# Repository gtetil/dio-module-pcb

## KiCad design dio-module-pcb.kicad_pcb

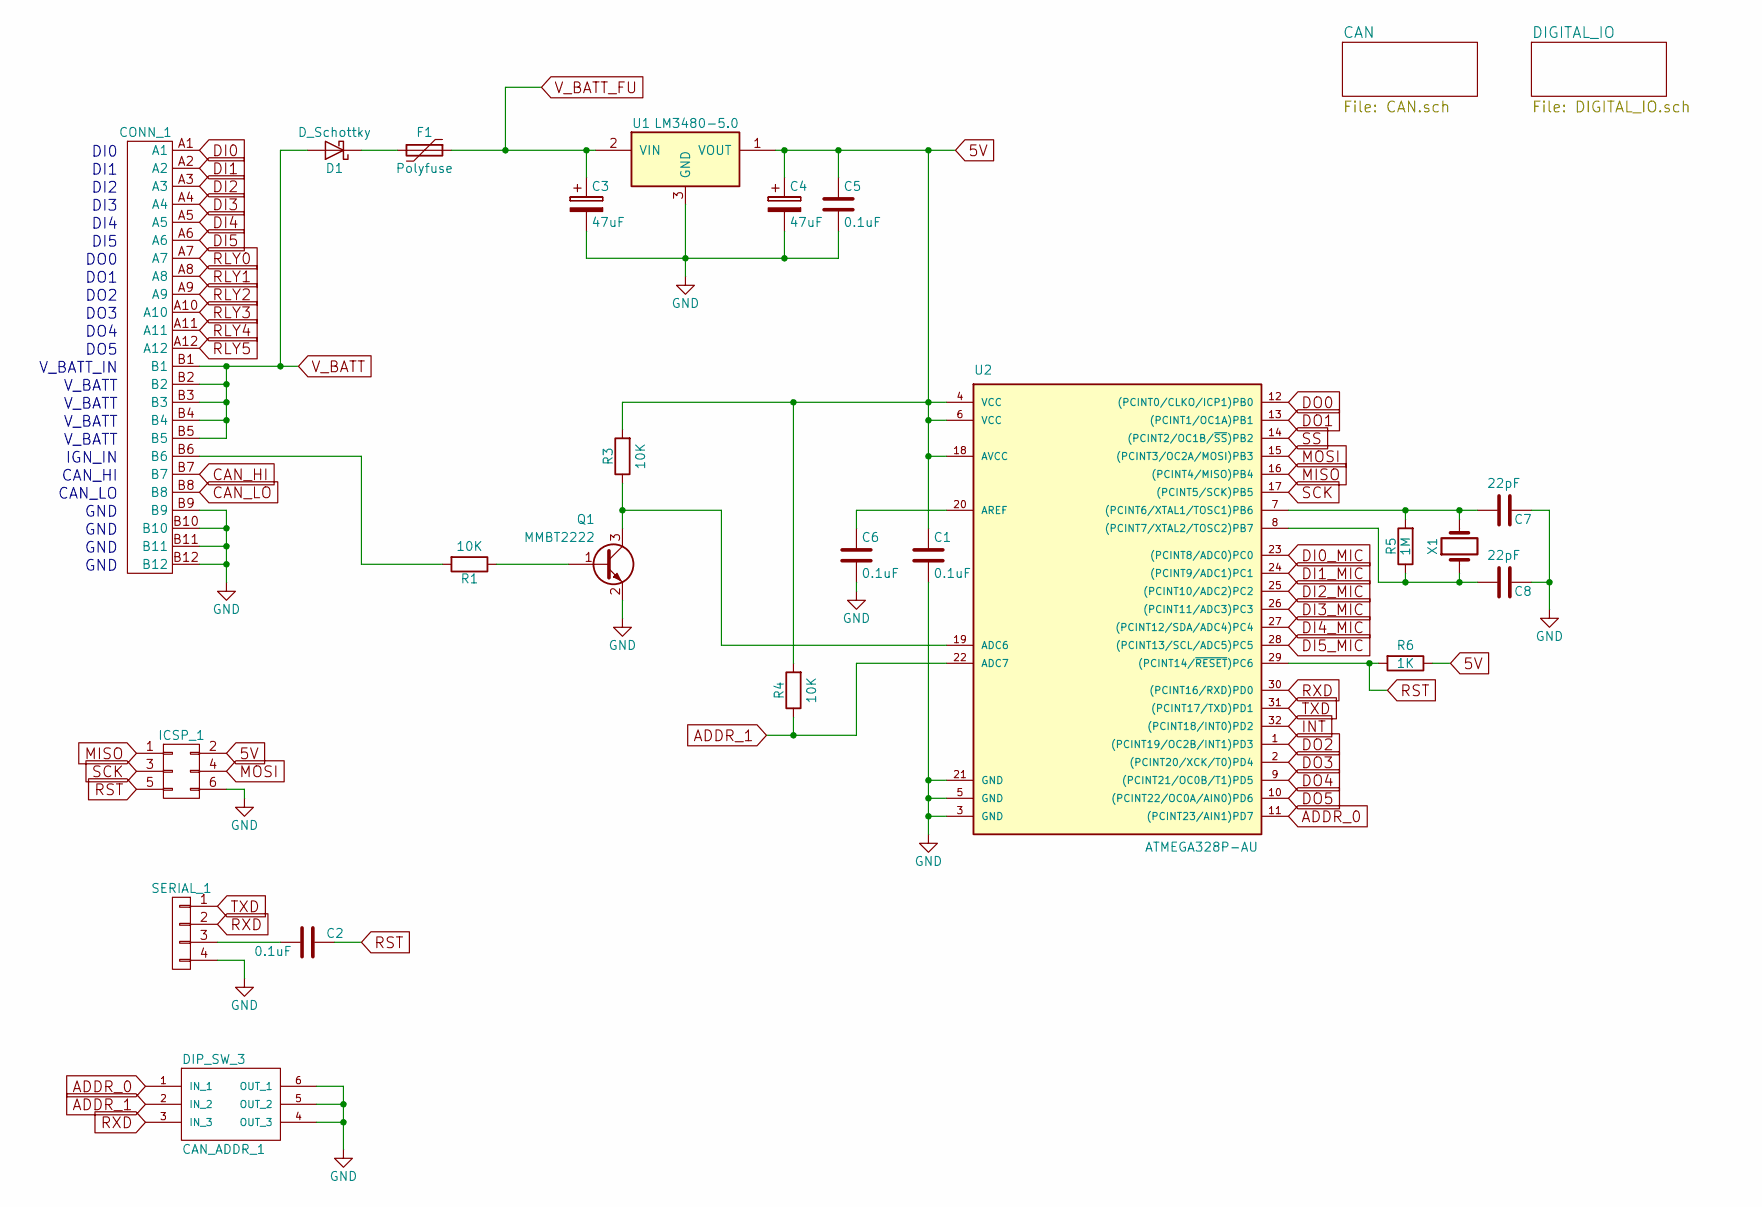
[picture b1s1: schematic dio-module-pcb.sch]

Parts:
C1, C2, C5, C6: 0.1uF; C_0805
C3, C4: 47uF; CP_Elec_6.3x5.3
C7, C8: 22pF; C_0805
CAN_ADDR_1: DIP_SW_3; SW_DIP_x3_W8.61mm_Slide_LowProfile
CONN_1: DEUTSCH_CONN_(DTM13-12PA-12PB-R008)
D1: D_Schottky; DO-214AB
F1: Polyfuse; R_1812
ICSP_1: CONN_02X03; Pin_Header_Straight_2x03_Pitch2.54mm_SMD
Q1: MMBT2222; SOT-23
R1, R3, R4: 10K; R_0805
R5: 1M; R_0805
R6: 1K; R_0805
SERIAL_1: CONN_01X04; Pin_Header_Straight_1x04_Pitch2.54mm_SMD_Pin1Right
U1: LM3480-5.0; SOT-23
U2: ATMEGA328P-AU; TQFP-32_7x7mm_Pitch0.8mm
X1: Crystal; Crystal_SMD_HC49-SD

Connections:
5V: C1.1, C4.1, C5.1, ICSP_1.2, R3.2, R4.2, R6.1, U1.1 (VOUT), U2.4 (VCC), U2.6 (VCC), U2.18 (AVCC); also elsewhere on the board
ADDR_0: CAN_ADDR_1.1 (IN_1), U2.11 ((PCINT23/AIN1)PD7)
ADDR_1: CAN_ADDR_1.2 (IN_2), R4.1, U2.22 (ADC7)
CAN_HI: CONN_1.B7; also elsewhere on the board
CAN_LO: CONN_1.B8; also elsewhere on the board
DI0: CONN_1.A1; also elsewhere on the board
DI0_MIC: U2.23 ((PCINT8/ADC0)PC0); also elsewhere on the board
DI1: CONN_1.A2; also elsewhere on the board
DI1_MIC: U2.24 ((PCINT9/ADC1)PC1); also elsewhere on the board
DI2: CONN_1.A3; also elsewhere on the board
DI2_MIC: U2.25 ((PCINT10/ADC2)PC2); also elsewhere on the board
DI3: CONN_1.A4; also elsewhere on the board
DI3_MIC: U2.26 ((PCINT11/ADC3)PC3); also elsewhere on the board
DI4: CONN_1.A5; also elsewhere on the board
DI4_MIC: U2.27 ((PCINT12/SDA/ADC4)PC4); also elsewhere on the board
DI5: CONN_1.A6; also elsewhere on the board
DI5_MIC: U2.28 ((PCINT13/SCL/ADC5)PC5); also elsewhere on the board
DO0: U2.12 ((PCINT0/CLKO/ICP1)PB0); also elsewhere on the board
DO1: U2.13 ((PCINT1/OC1A)PB1); also elsewhere on the board
DO2: U2.1 ((PCINT19/OC2B/INT1)PD3); also elsewhere on the board
DO3: U2.2 ((PCINT20/XCK/T0)PD4); also elsewhere on the board
DO4: U2.9 ((PCINT21/OC0B/T1)PD5); also elsewhere on the board
DO5: U2.10 ((PCINT22/OC0A/AIN0)PD6); also elsewhere on the board
GND: C1.2, C3.2, C4.2, C5.2, C6.2, C7.1, C8.1, CAN_ADDR_1.4 (OUT_3), CAN_ADDR_1.5 (OUT_2), CAN_ADDR_1.6 (OUT_1), CONN_1.B9, CONN_1.B10, CONN_1.B11, CONN_1.B12, ICSP_1.6, Q1.2 (E), SERIAL_1.4, U1.3 (GND), U2.3 (GND), U2.5 (GND), U2.21 (GND); also elsewhere on the board
INT: U2.32 ((PCINT18/INT0)PD2); also elsewhere on the board
MISO: ICSP_1.1, U2.16 ((PCINT4/MISO)PB4); also elsewhere on the board
MOSI: ICSP_1.4, U2.15 ((PCINT3/OC2A/MOSI)PB3); also elsewhere on the board
unnamed: C2.2, SERIAL_1.3
unnamed: C6.1, U2.20 (AREF)
unnamed: C7.2, R5.2, U2.7 ((PCINT6/XTAL1/TOSC1)PB6), X1.2
unnamed: C8.2, R5.1, U2.8 ((PCINT7/XTAL2/TOSC2)PB7), X1.1
unnamed: CONN_1.B6, R1.2
unnamed: D1.1 (K), F1.2
unnamed: Q1.1 (B), R1.1
unnamed: Q1.3 (C), R3.1, U2.19 (ADC6)
RLY0: CONN_1.A7; also elsewhere on the board
RLY1: CONN_1.A8; also elsewhere on the board
RLY2: CONN_1.A9; also elsewhere on the board
RLY3: CONN_1.A10; also elsewhere on the board
RLY4: CONN_1.A11; also elsewhere on the board
RLY5: CONN_1.A12; also elsewhere on the board
RST: C2.1, ICSP_1.5, R6.2, U2.29 ((PCINT14/~RESET~)PC6)
RXD: CAN_ADDR_1.3 (IN_3), SERIAL_1.2, U2.30 ((PCINT16/RXD)PD0)
SCK: ICSP_1.3, U2.17 ((PCINT5/SCK)PB5); also elsewhere on the board
SS: U2.14 ((PCINT2/OC1B/~SS~)PB2); also elsewhere on the board
TXD: SERIAL_1.1, U2.31 ((PCINT17/TXD)PD1)
V_BATT: CONN_1.B1, CONN_1.B2, CONN_1.B3, CONN_1.B4, CONN_1.B5, D1.2 (A); also elsewhere on the board
V_BATT_FU: C3.1, F1.1, U1.2 (VIN); also elsewhere on the board

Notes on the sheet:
DI0
DI1
DI2
DI3
DI4
DI5
DO0
DO1
DO2
DO3
DO4
DO5
V_BATT_IN
V_BATT
IGN_IN
CAN_HI
CAN_LO
GND

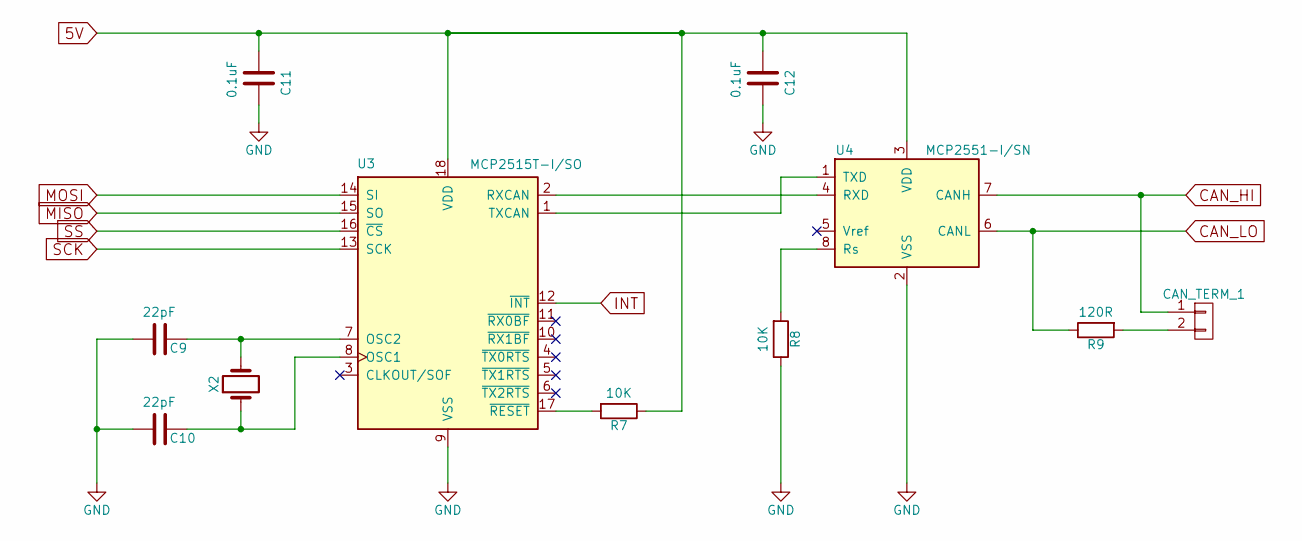
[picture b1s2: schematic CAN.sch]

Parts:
C9, C10: 22pF; C_0805
C11, C12: 0.1uF; C_0805
CAN_TERM_1: CONN_01X02; Pin_Header_Straight_1x02_Pitch2.54mm_SMD_Pin1Right
R7, R8: 10K; R_0805
R9: 120R; R_0805
U3: MCP2515T-I/SO; SOIC-18W_7.5x11.6mm_Pitch1.27mm
U4: MCP2551-I/SN; SOIC-8_3.9x4.9mm_Pitch1.27mm
X2: Crystal; Crystal_SMD_HC49-SD

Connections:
5V: C11.2, C12.2, R7.1, U3.18 (VDD), U4.3 (VDD); also elsewhere on the board
CAN_HI: CAN_TERM_1.1, U4.7 (CANH); also elsewhere on the board
CAN_LO: R9.1, U4.6 (CANL); also elsewhere on the board
GND: C9.2, C10.2, C11.1, C12.1, R8.1, U3.9 (VSS), U4.2 (VSS); also elsewhere on the board
INT: U3.12 (~INT); also elsewhere on the board
MISO: U3.15 (SO); also elsewhere on the board
MOSI: U3.14 (SI); also elsewhere on the board
unnamed: C9.1, U3.7 (OSC2), X2.2
unnamed: C10.1, U3.8 (OSC1), X2.1
unnamed: CAN_TERM_1.2, R9.2
unnamed: R7.2, U3.17 (~RESET)
unnamed: R8.2, U4.8 (Rs)
unnamed: U3.1 (TXCAN), U4.1 (TXD)
unnamed: U3.2 (RXCAN), U4.4 (RXD)
SCK: U3.13 (SCK); also elsewhere on the board
SS: U3.16 (~CS); also elsewhere on the board

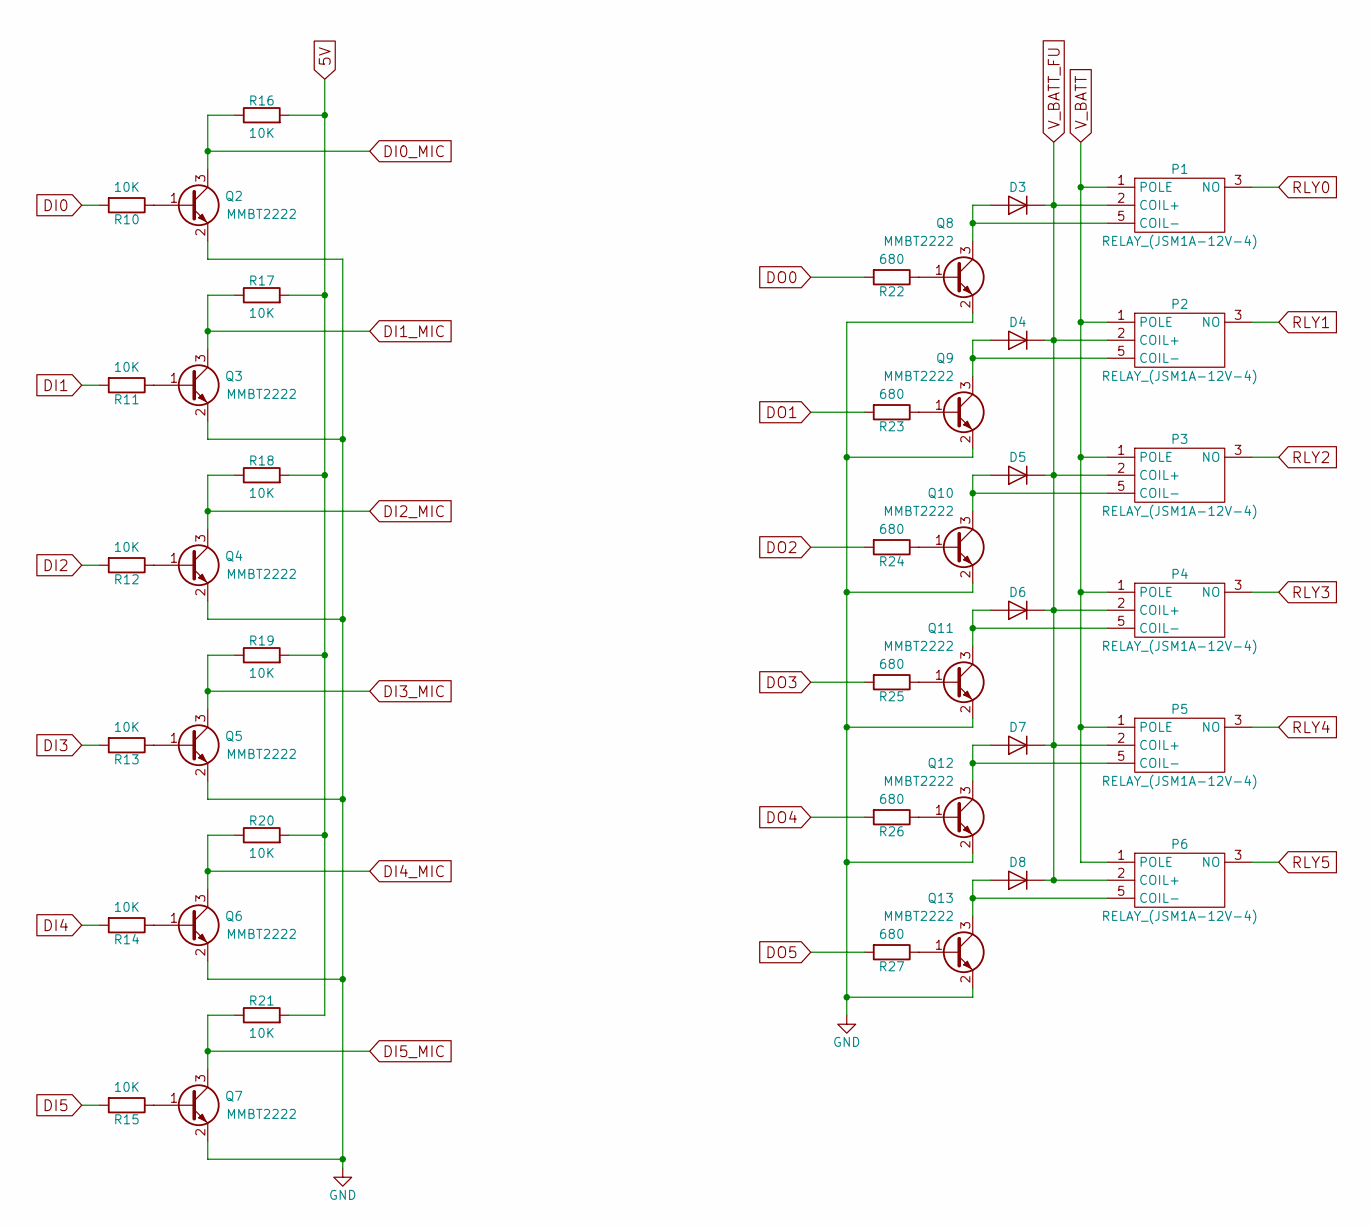
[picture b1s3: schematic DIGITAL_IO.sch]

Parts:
D3, D4, D5, D6, D7, D8: D; D_SOD-123
P1, P2, P3, P4, P5, P6: RELAY_(JSM1A-12V-4)
Q2, Q3, Q4, Q5, Q6, Q7, Q8, Q9, Q10, Q11, Q12, Q13: MMBT2222; SOT-23
R10, R11, R12, R13, R14, R15, R16, R17, R18, R19, R20, R21: 10K; R_0805
R22, R23, R24, R25, R26, R27: 680; R_0805

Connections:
5V: R16.2, R17.2, R18.2, R19.2, R20.2, R21.2; also elsewhere on the board
DI0: R10.2; also elsewhere on the board
DI0_MIC: Q2.3 (C), R16.1; also elsewhere on the board
DI1: R11.2; also elsewhere on the board
DI1_MIC: Q3.3 (C), R17.1; also elsewhere on the board
DI2: R12.2; also elsewhere on the board
DI2_MIC: Q4.3 (C), R18.1; also elsewhere on the board
DI3: R13.2; also elsewhere on the board
DI3_MIC: Q5.3 (C), R19.1; also elsewhere on the board
DI4: R14.2; also elsewhere on the board
DI4_MIC: Q6.3 (C), R20.1; also elsewhere on the board
DI5: R15.2; also elsewhere on the board
DI5_MIC: Q7.3 (C), R21.1; also elsewhere on the board
DO0: R22.2; also elsewhere on the board
DO1: R23.2; also elsewhere on the board
DO2: R24.2; also elsewhere on the board
DO3: R25.2; also elsewhere on the board
DO4: R26.2; also elsewhere on the board
DO5: R27.2; also elsewhere on the board
GND: Q2.2 (E), Q3.2 (E), Q4.2 (E), Q5.2 (E), Q6.2 (E), Q7.2 (E), Q8.2 (E), Q9.2 (E), Q10.2 (E), Q11.2 (E), Q12.2 (E), Q13.2 (E); also elsewhere on the board
unnamed: D3.2 (A), P1.5 (COIL-), Q8.3 (C)
unnamed: D4.2 (A), P2.5 (COIL-), Q9.3 (C)
unnamed: D5.2 (A), P3.5 (COIL-), Q10.3 (C)
unnamed: D6.2 (A), P4.5 (COIL-), Q11.3 (C)
unnamed: D7.2 (A), P5.5 (COIL-), Q12.3 (C)
unnamed: D8.2 (A), P6.5 (COIL-), Q13.3 (C)
unnamed: Q2.1 (B), R10.1
unnamed: Q3.1 (B), R11.1
unnamed: Q4.1 (B), R12.1
unnamed: Q5.1 (B), R13.1
unnamed: Q6.1 (B), R14.1
unnamed: Q7.1 (B), R15.1
unnamed: Q8.1 (B), R22.1
unnamed: Q9.1 (B), R23.1
unnamed: Q10.1 (B), R24.1
unnamed: Q11.1 (B), R25.1
unnamed: Q12.1 (B), R26.1
unnamed: Q13.1 (B), R27.1
RLY0: P1.3 (NO); also elsewhere on the board
RLY1: P2.3 (NO); also elsewhere on the board
RLY2: P3.3 (NO); also elsewhere on the board
RLY3: P4.3 (NO); also elsewhere on the board
RLY4: P5.3 (NO); also elsewhere on the board
RLY5: P6.3 (NO); also elsewhere on the board
V_BATT: P1.1 (POLE), P2.1 (POLE), P3.1 (POLE), P4.1 (POLE), P5.1 (POLE), P6.1 (POLE); also elsewhere on the board
V_BATT_FU: D3.1 (K), D4.1 (K), D5.1 (K), D6.1 (K), D7.1 (K), D8.1 (K), P1.2 (COIL+), P2.2 (COIL+), P3.2 (COIL+), P4.2 (COIL+), P5.2 (COIL+), P6.2 (COIL+); also elsewhere on the board

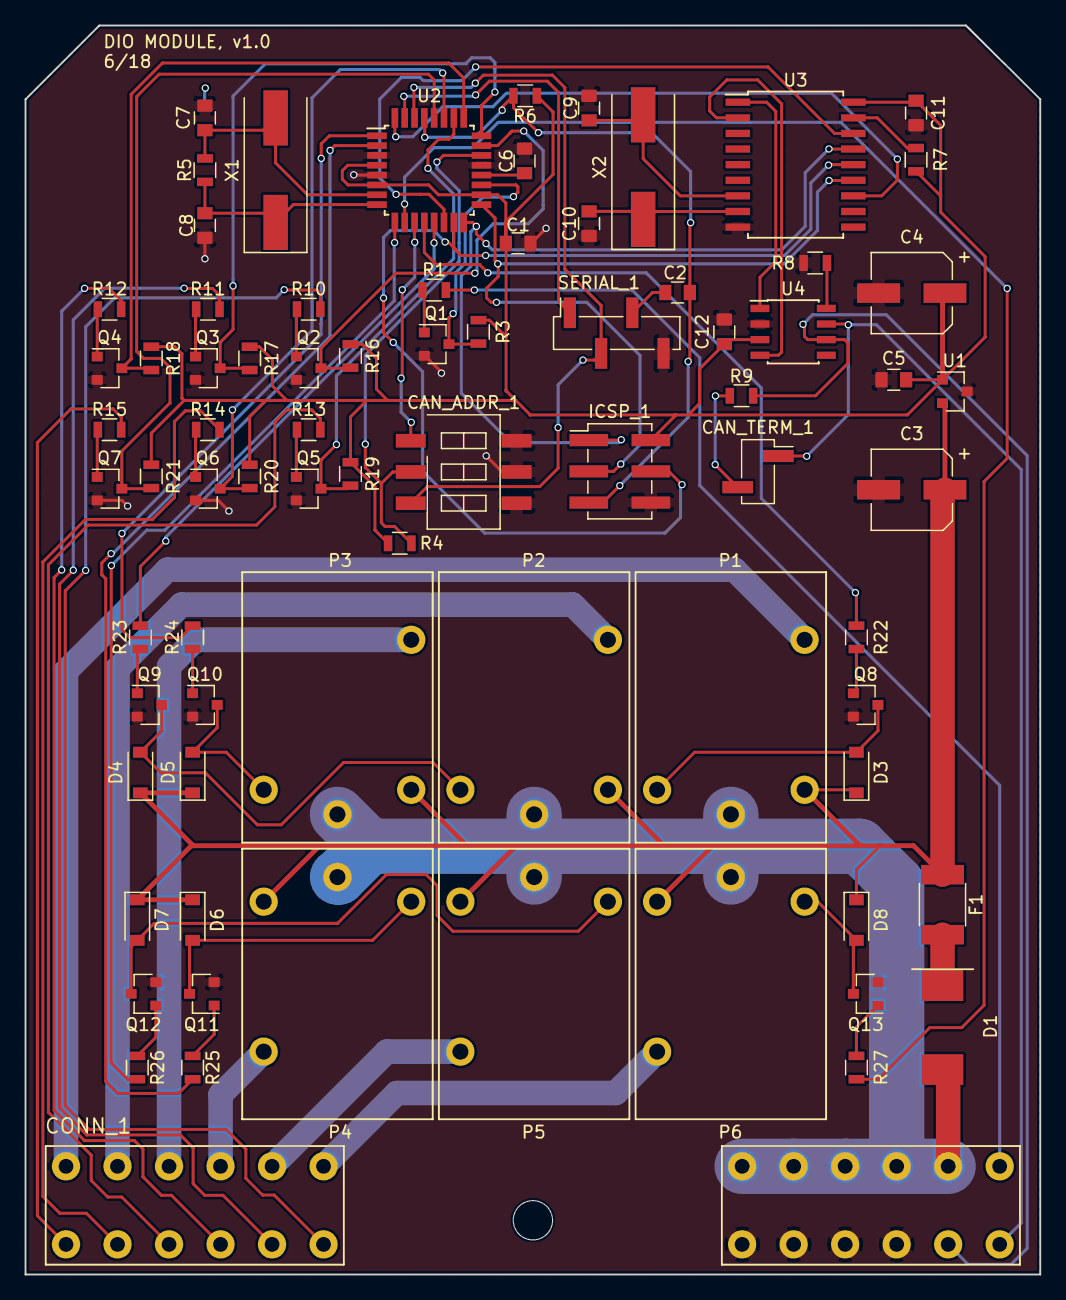
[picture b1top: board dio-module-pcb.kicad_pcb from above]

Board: 2 copper layers, 82.5 x 101.6 mm, 76 parts (0 on the bottom side), 73 nets.

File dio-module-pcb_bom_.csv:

Component,Description,Part,References,Value,Footprint,Quantity Per PCB,Datasheet
1,Unpolarized capacitor,C,"C1, C2, C5, C6, C11, C12",0.1uF,C_0805,6,
2,Unpolarized capacitor,C,"C7, C8, C9, C10",22pF,C_0805,4,
3,Polarised capacitor,CP,"C3, C4",47uF,CP_Elec_6.3x5.3,2,
4,"Connector, single row, 01x02, pin header",CONN_01X02,CAN_TERM_1,CONN_01X02,Pin_Header_Straight_1x02_Pitch2.54mm_SMD_Pin1Right,1,
5,,DIP_SW_3,CAN_ADDR_1,DIP_SW_3,SW_DIP_x3_W8.61mm_Slide_LowProfile,1,
6,,DEUTSCH_CONN_(DTM13-12PA-12PB-R008),CONN_1,DEUTSCH_CONN_(DTM13-12PA-12PB-R008),DEUTSCH_CONN_(DTM13-12PA-12PB-R008),1,
7,Diode,D,"D3, D4, D5, D6, D7, D8",D,D_SOD-123,6,
8,Schottky diode,D_Schottky,D1,D_Schottky,DO-214AB,1,
9,"resettable fuse, polymeric positive temperature coefficient (PPTC)",Polyfuse,F1,Polyfuse,R_1812,1,
10,"Connector, double row, 02x03, pin header",CONN_02X03,ICSP_1,CONN_02X03,Pin_Header_Straight_2x03_Pitch2.54mm_SMD,1,
11,,RELAY_(JSM1A-12V-4),"P1, P2, P3, P4, P5, P6",RELAY_(JSM1A-12V-4),RELAY_(JSM1A-12V-4),6,
12,Transistor NPN (general),Q_NPN_BEC,"Q1, Q2, Q3, Q4, Q5, Q6, Q7, Q8, Q9, Q10, Q11, Q12, Q13",MMBT2222,SOT-23,13,
13,Resistor,R,"R1, R3, R4, R7, R8, R10, R11, R12, R13, R14, R15, R16, R17, R18, R19, R20, R21",10K,R_0805,17,
14,Resistor,R,R9,120R,R_0805,1,
15,Resistor,R,R6,1K,R_0805,1,
16,Resistor,R,R5,1M,R_0805,1,
17,Resistor,R,"R22, R23, R24, R25, R26, R27",680,R_0805,6,
18,"Connector, single row, 01x04, pin header",CONN_01X04,SERIAL_1,CONN_01X04,Pin_Header_Straight_1x04_Pitch2.54mm_SMD_Pin1Right,1,
19,"TQFP32, 16k Flash, 1kB SRAM, 512B EEPROM",ATMEGA328P-AU,U2,ATMEGA328P-AU,TQFP-32_7x7mm_Pitch0.8mm,1,http://www.atmel.com/images/atmel-8271-8-bit-avr-microcontro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
20,"100mA, Quasi Low Dropout Voltage Regulator, 3.3V positive fixed output, SOT-23 package",LM3480-5.0,U1,LM3480-5.0,SOT-23,1,http://www.ti.com/lit/ds/symlink/lm3480.pdf
21,"Stand-Alone CAN Controller with SPI Interface, SOIC-18, Extended temperature range",MCP2515T-I/SO,U3,MCP2515T-I/SO,SOIC-18W_7.5x11.6mm_Pitch1.27mm,1,http://ww1.microchip.com/downloads/en/DeviceDoc/21801e.pdf
22,"High-Speed CAN Transceiver, 1Mbps, 5V supply, SOIC8 package",MCP2551-I/SN,U4,MCP2551-I/SN,SOIC-8_3.9x4.9mm_Pitch1.27mm,1,http://ww1.microchip.com/downloads/en/devicedoc/21667d.pdf
23,Two pin crystal,Crystal,"X1, X2",Crystal,Crystal_SMD_HC49-SD,2,





Component Groups:,23
Component Count:,76
Fitted Components:,76
Number of PCBs:,1
Total components:,76
Schematic Version:,
Schematic Date:,
BoM Date:,6/8/2018 12:59:09 PM
Schematic Source:,C:/Users/gtetil/Documents/Projects/dio-module-pcb/dio-module-pcb.sch
KiCad Version:,Eeschema 4.0.6

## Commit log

2018-06-06 - Initial commit.
2018-06-08 - Finished circuit and PCB.
